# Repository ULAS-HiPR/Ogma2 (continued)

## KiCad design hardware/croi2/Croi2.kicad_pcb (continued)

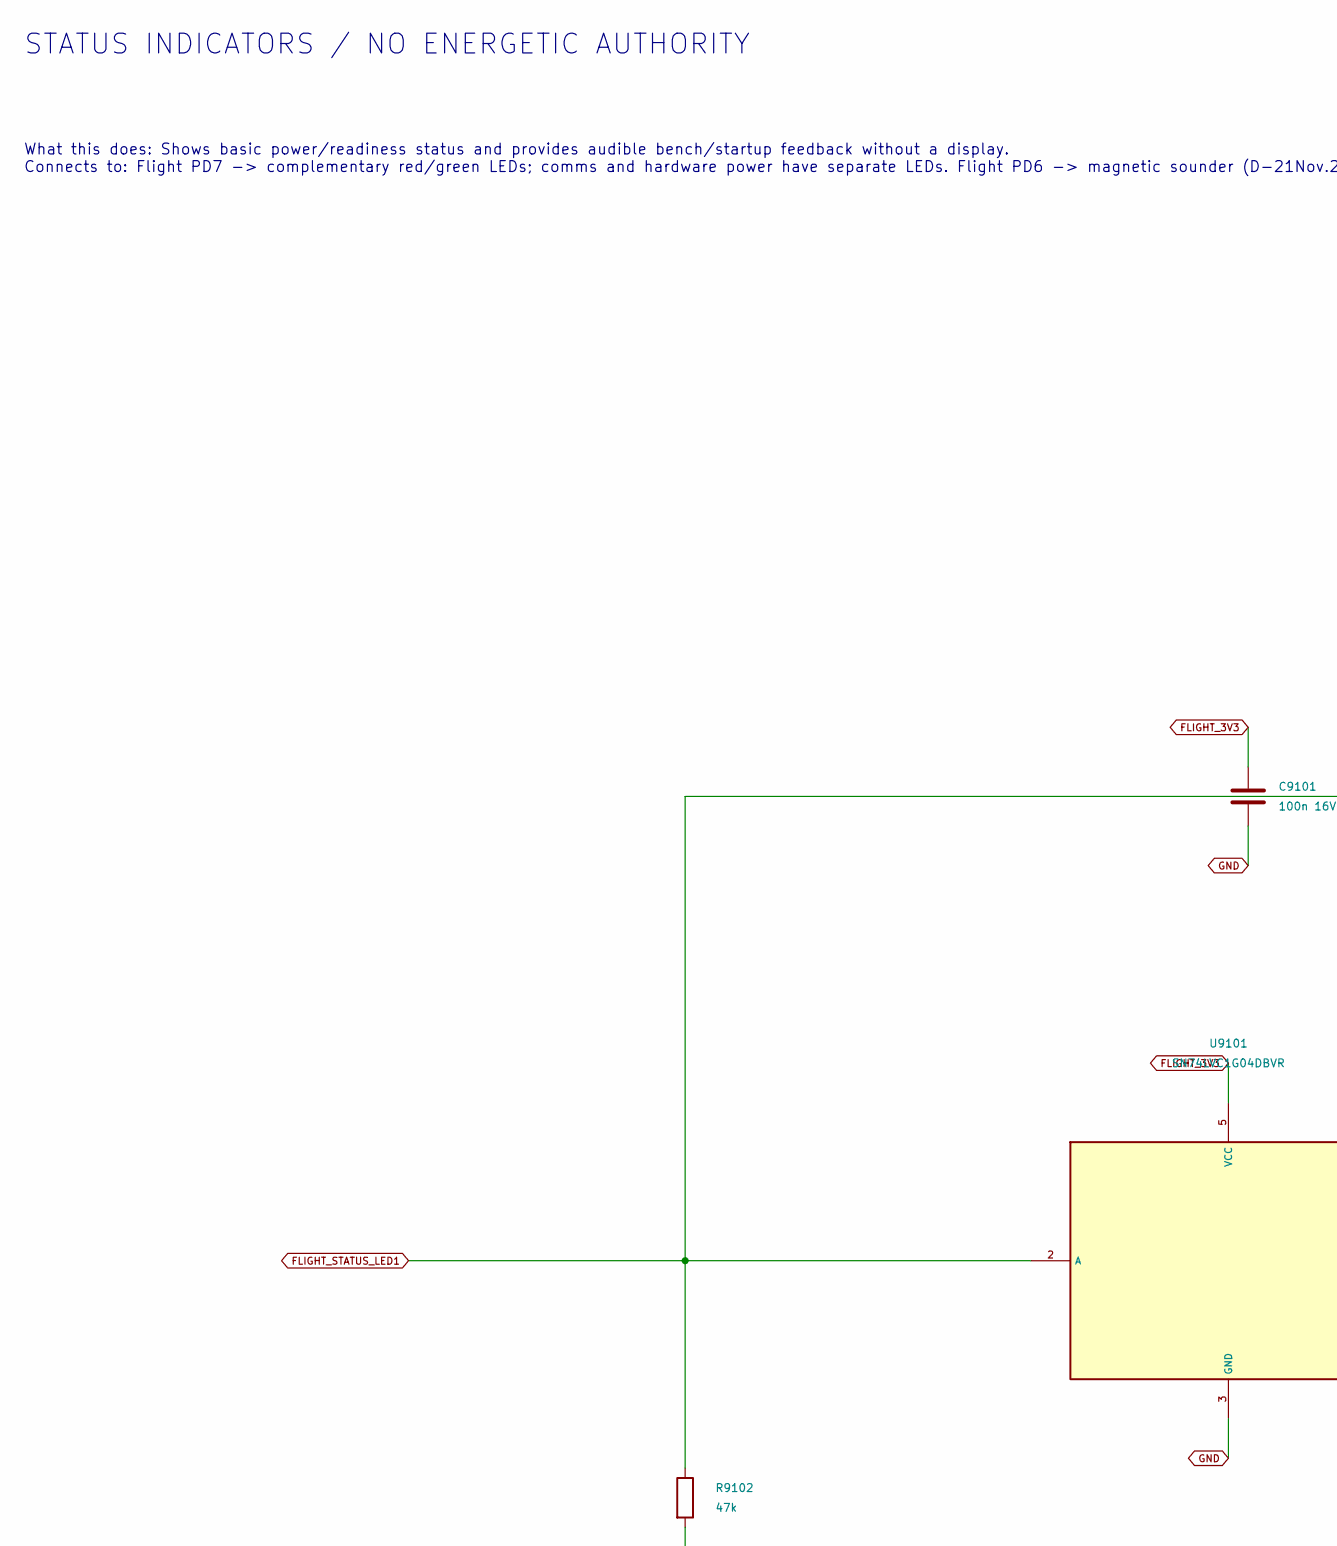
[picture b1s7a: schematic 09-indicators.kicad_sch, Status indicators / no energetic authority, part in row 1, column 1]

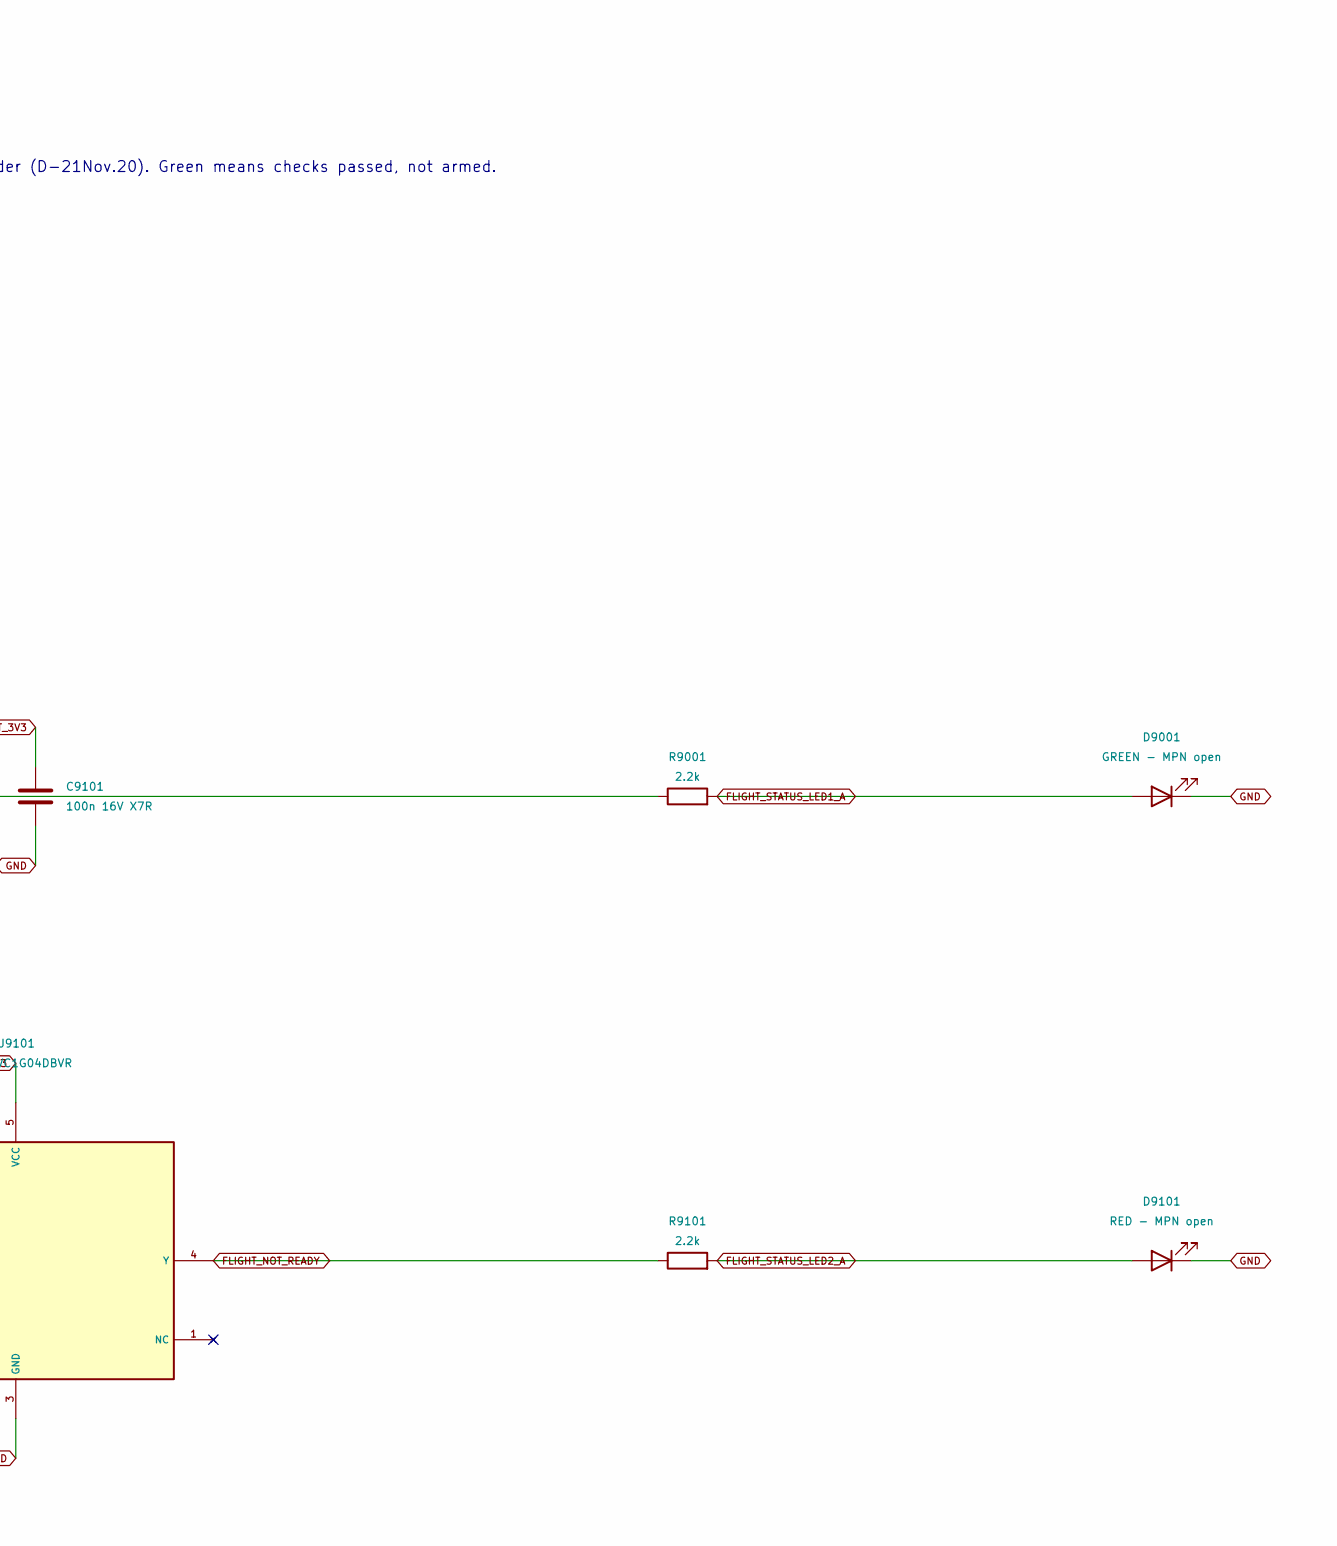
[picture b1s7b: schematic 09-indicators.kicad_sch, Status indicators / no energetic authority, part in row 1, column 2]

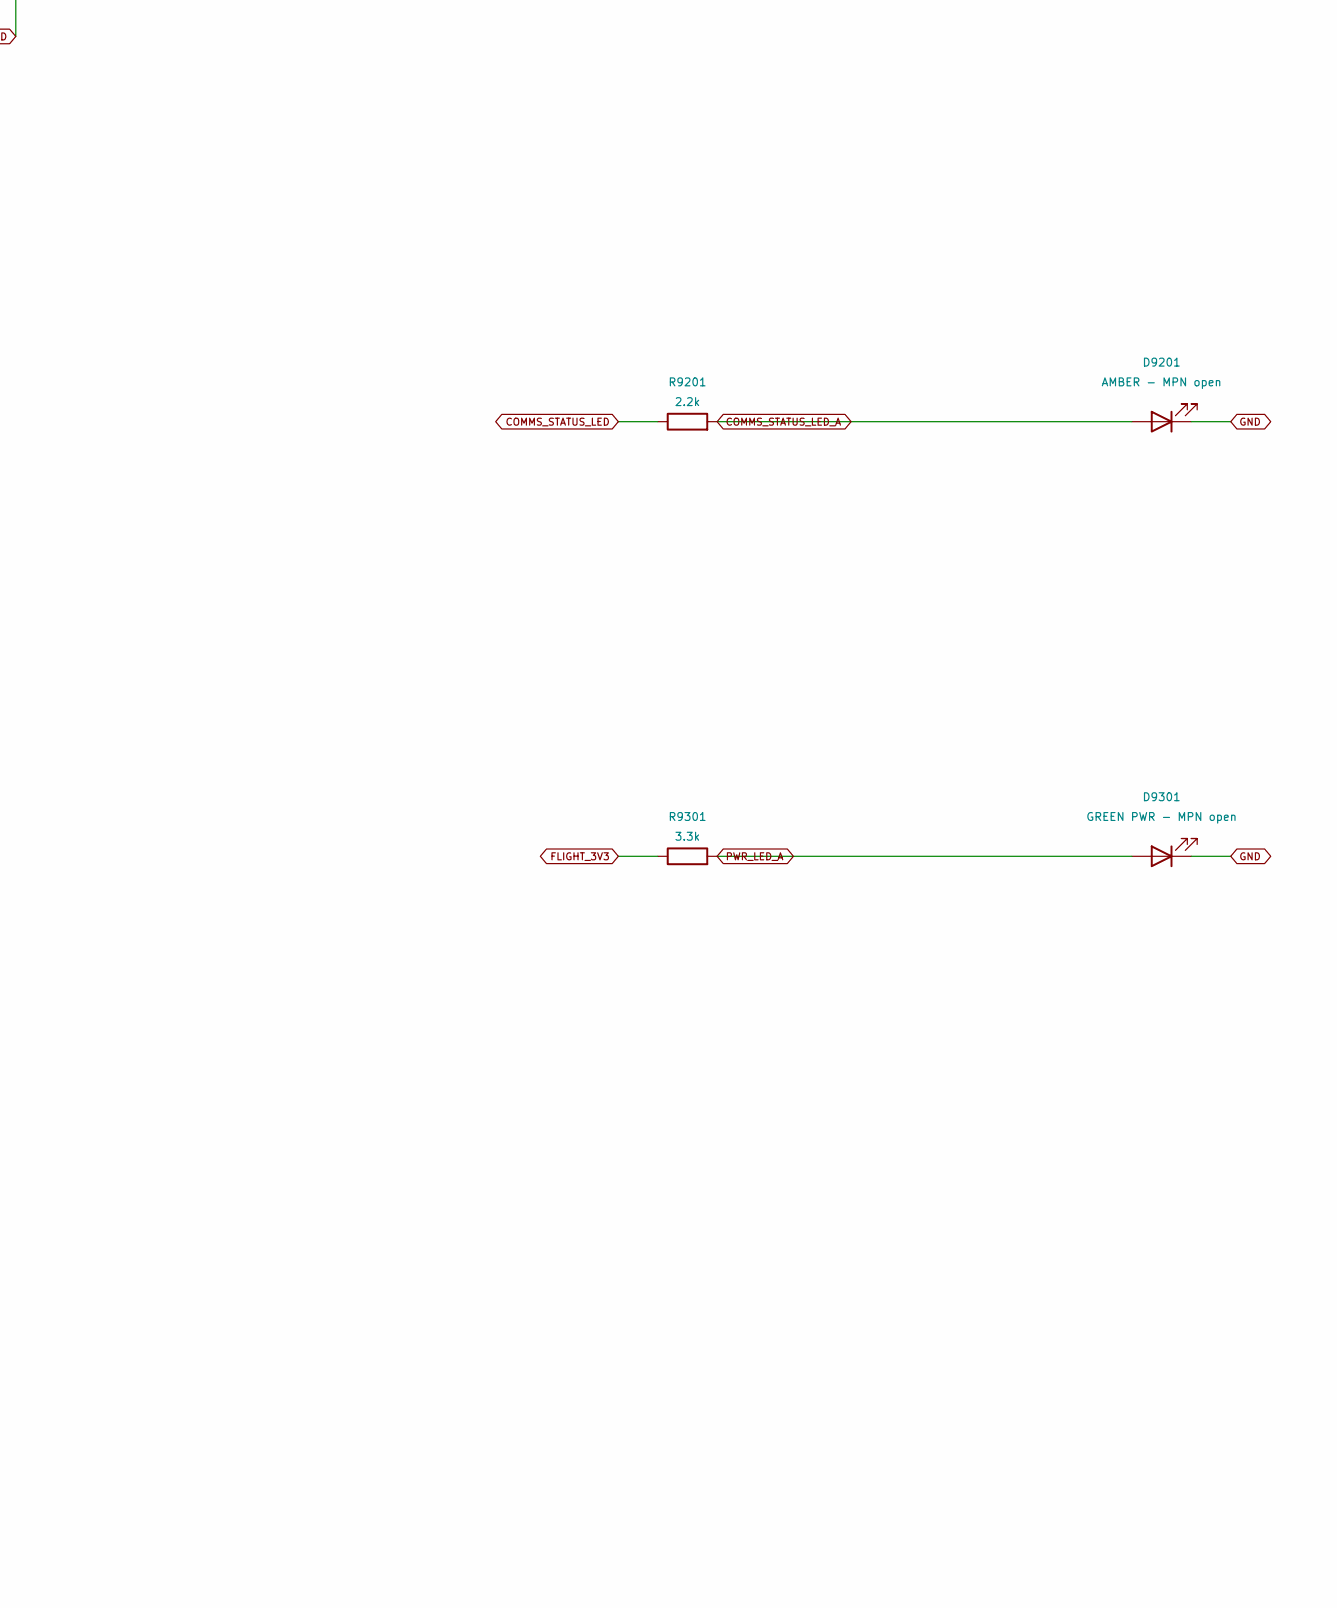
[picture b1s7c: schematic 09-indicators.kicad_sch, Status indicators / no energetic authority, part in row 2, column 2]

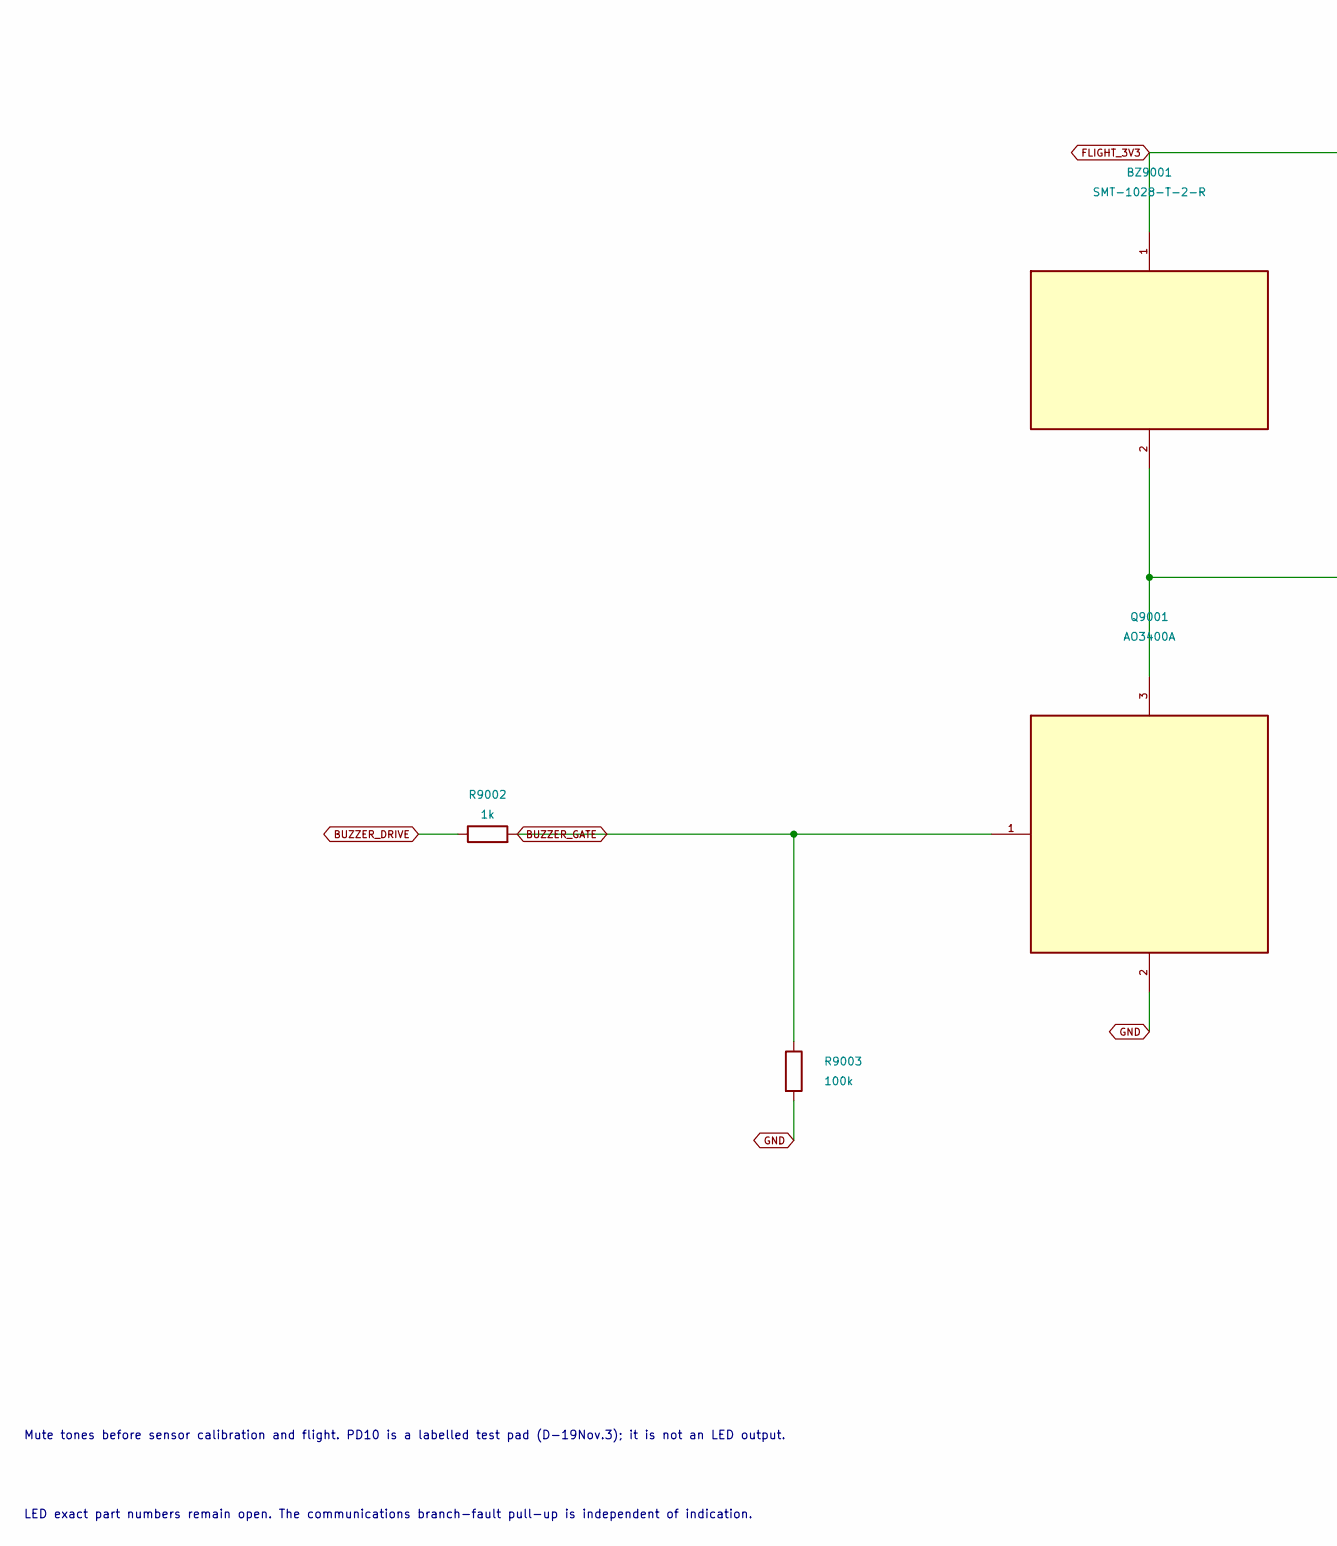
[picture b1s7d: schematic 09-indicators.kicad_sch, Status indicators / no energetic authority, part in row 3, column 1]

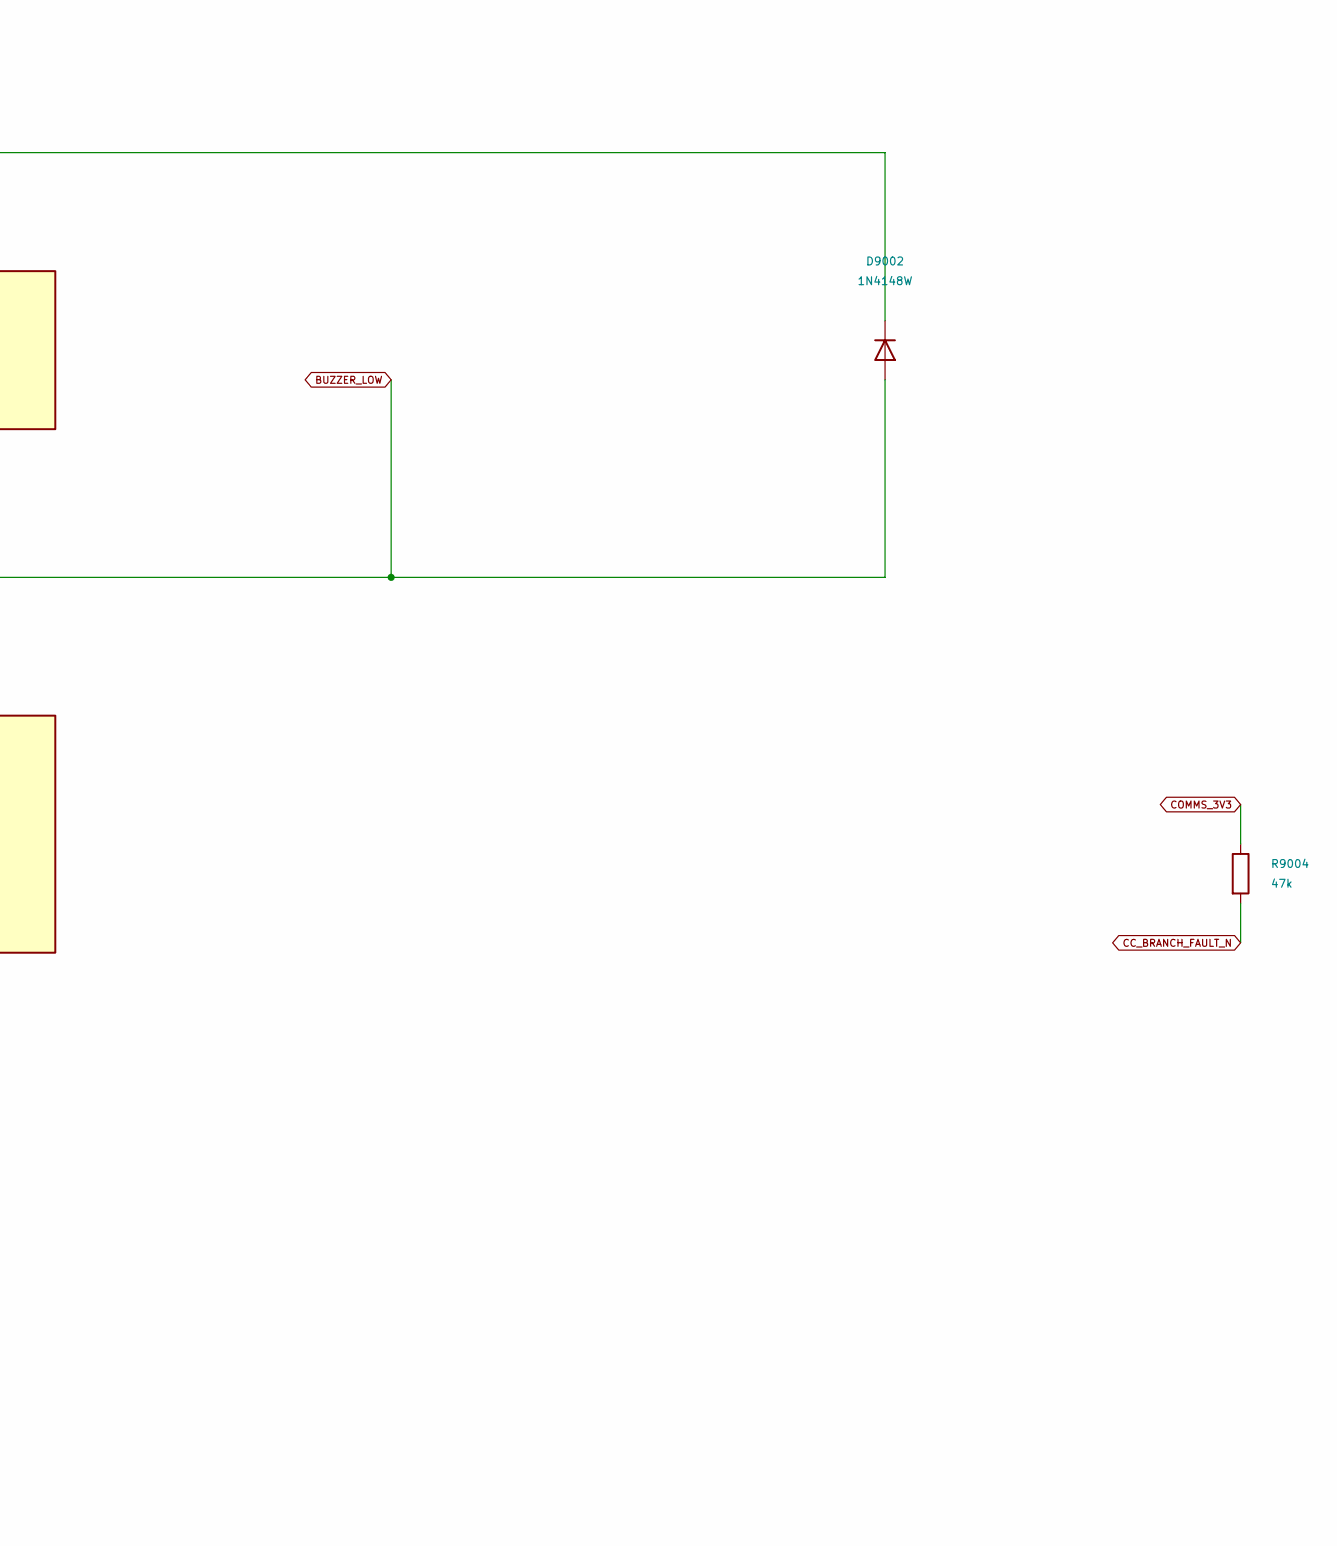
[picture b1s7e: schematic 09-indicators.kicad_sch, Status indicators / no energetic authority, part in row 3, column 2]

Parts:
BZ9001: SMT-1028-T-2-R; MagneticBuzzer_PUI_SMT-1028-T-2-R; MPN SMT-1028-T-2-R
C9101: 100n 16V X7R; C_0402_1005Metric; MPN CL05B104KB54PNC; LCSC C307331
D9001: GREEN - MPN open; LED_0603_1608Metric
D9002: 1N4148W; D_SOD-123
D9101: RED - MPN open; LED_0603_1608Metric
D9201: AMBER - MPN open; LED_0603_1608Metric
D9301: GREEN PWR - MPN open; LED_0603_1608Metric
Q9001: AO3400A; SOT-23; MPN AO3400A
R9001, R9101, R9201: 2.2k; R_0402_1005Metric; MPN 0402WGF2201TCE; LCSC C25879
R9002: 1k; R_0402_1005Metric; MPN 0402WGF1001TCE; LCSC C11702
R9003: 100k; R_0402_1005Metric; MPN 0402WGF1003TCE; LCSC C25741
R9004, R9102: 47k; R_0402_1005Metric; MPN 0402WGF4702TCE; LCSC C25792
R9301: 3.3k; R_0402_1005Metric; MPN 0402WGF3301TCE; LCSC C25890
U9101: SN74LVC1G04DBVR; SOT-23-5; MPN SN74LVC1G04DBVR

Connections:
BUZZER_DRIVE: R9002.1; also elsewhere on the board
BUZZER_GATE: Q9001.1 (G), R9002.2, R9003.1
BUZZER_LOW: BZ9001.2 (-), D9002.2 (A), Q9001.3 (D)
CC_BRANCH_FAULT_N: R9004.2; also elsewhere on the board
COMMS_3V3: R9004.1; also elsewhere on the board
COMMS_STATUS_LED: R9201.1; also elsewhere on the board
COMMS_STATUS_LED_A: D9201.2 (A), R9201.2
FLIGHT_3V3: BZ9001.1 (+), C9101.1, D9002.1 (K), R9301.1, U9101.5 (VCC); also elsewhere on the board
FLIGHT_NOT_READY: R9101.1, U9101.4 (Y)
FLIGHT_STATUS_LED1: R9001.1, R9102.1, U9101.2 (A); also elsewhere on the board
FLIGHT_STATUS_LED1_A: D9001.2 (A), R9001.2
FLIGHT_STATUS_LED2_A: D9101.2 (A), R9101.2
GND: C9101.2, D9001.1 (K), D9101.1 (K), D9201.1 (K), D9301.1 (K), Q9001.2 (S), R9003.2, R9102.2, U9101.3 (GND); also elsewhere on the board
PWR_LED_A: D9301.2 (A), R9301.2

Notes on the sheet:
STATUS INDICATORS / NO ENERGETIC AUTHORITY
Green is not arming or launch authority. A stuck GPIO can show stale health if firmware hangs.
LED exact part numbers remain open. The communications branch-fault pull-up is independent of indication.
PD7 low/reset selects red. PD7 high selects green after profile checks pass.
Mute tones before sensor calibration and flight. PD10 is a labelled test pad (D-19Nov.3); it is not an LED output.
What this does: Shows basic power/readiness status and provides audible bench/startup feedback without a display. Connects to: Flight PD7 -> complementary red/green LEDs; comms and hardware power have separate LEDs. Flight PD6 -> magnetic sounder (D-21Nov.20). Green means checks passed, not armed.
AUDIBLE FEEDBACK
